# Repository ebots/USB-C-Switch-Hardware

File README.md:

# USB C switcher hardware

### Rev C

### Rev A & B

## About 

The USB switcher is a bidirectional USB-C switcher. It can be pragmatically controlled to switch connection between USB devices and hosts.  

## Firmware 

Firmware is available [in the Firmware repo](https://gitlab.com/CodethinkLabs/usb-switch/firmware). Follow the steps in the [README](https://gitlab.com/CodethinkLabs/usb-switch/firmware/-/tree/main/reva-firmware) to flash.

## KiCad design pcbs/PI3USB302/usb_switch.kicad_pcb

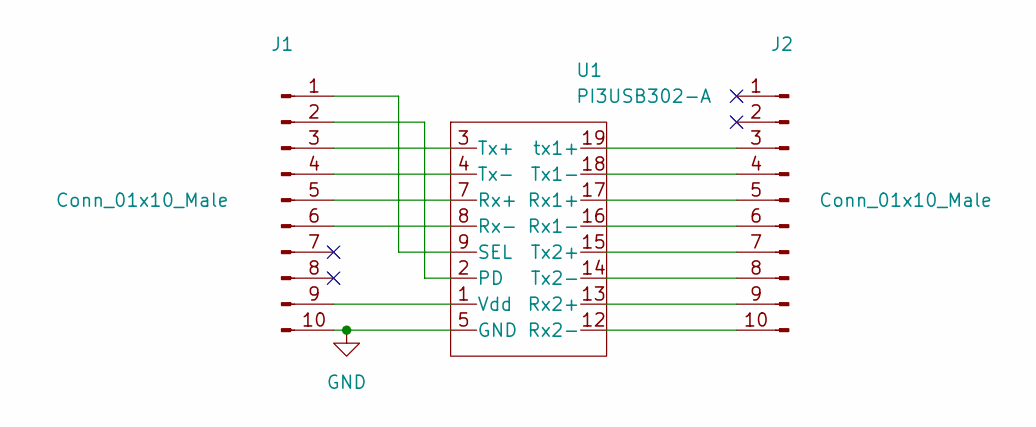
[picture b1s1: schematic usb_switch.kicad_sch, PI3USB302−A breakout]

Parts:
J1, J2: Conn_01x10_Male; PinHeader_1x10_P2.54mm_Vertical
U1: PI3USB302−A

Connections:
GND: J1.10, U1.5 (GND)
unnamed: J1.1, U1.9 (SEL)
unnamed: J1.2, U1.2 (PD)
unnamed: J1.3, U1.3 (Tx+)
unnamed: J1.4, U1.4 (Tx-)
unnamed: J1.5, U1.7 (Rx+)
unnamed: J1.6, U1.8 (Rx-)
unnamed: J1.9, U1.1 (Vdd)
unnamed: J2.3, U1.19 (tx1+)
unnamed: J2.4, U1.18 (Tx1-)
unnamed: J2.5, U1.17 (Rx1+)
unnamed: J2.6, U1.16 (Rx1-)
unnamed: J2.7, U1.15 (Tx2+)
unnamed: J2.8, U1.14 (Tx2-)
unnamed: J2.9, U1.13 (Rx2+)
unnamed: J2.10, U1.12 (Rx2-)

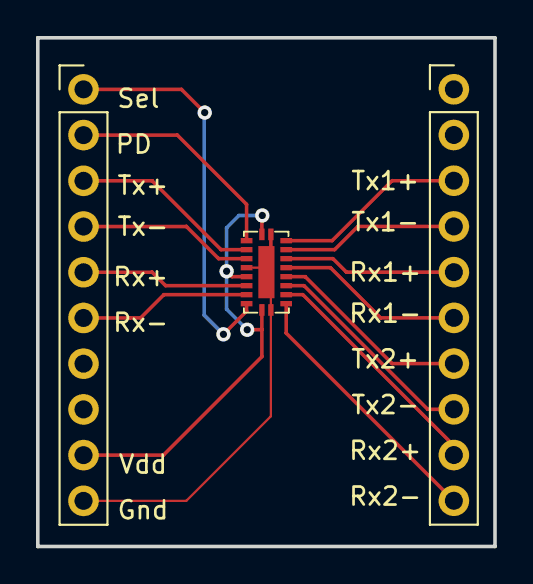
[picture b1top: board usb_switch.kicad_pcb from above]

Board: 2 copper layers, 25.4 x 28.3 mm, 3 parts (0 on the bottom side), 16 nets.
